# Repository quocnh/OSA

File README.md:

# ESP32_MedicalDevice
IoT devices to collect SPo2 and ECG for cancer treatment.

Downloading Repo from Github
---------------------------------------------------------------------------------------------------------------------------
- 1.) Navigate to "https://github.com/quocnh/OSA_Medical_Devices"
- 2.) Copy HTTPS link
- 3.) Open Git Bash in a local folder
- 4.) enter "git clone <Insert HTTP link here>"
---------------------------------------------------------------------------------------------------------------------------

Installing Firmware to ESP32
---------------------------------------------------------------------------------------------------------------------------
- 1.) Add ESP32 boards to Arduino IDE
	-File -> Preferences 
	-Enter "https://dl.espressif.com/dl/package_esp32_index.json" into "Additional Board Manager URLs" field
	-Tools -> Board -> Boards Manager...
	-Find "esp32" and install version 1.05
- 2.) Add necessary libraries to Arduino IDE
	-Sketch -> Include Library -> Add .ZIP library
	-Select .ZIP from "libraries" folder
	-Repeat for all libraries in the "libraries" folder

   	ArduinoHtppClient (0.5.0)
  	NTPClient(3.2.1)
  	AduinoJson(6.21.4)
  	AutoConnect(1.4.2)
  	PageBuilder(1.5.6)
  	PubSubCleint(2.8)
  	TPBubSupClient(2.9.1)
  	Thingsboard(0.10.2)
  
- 3.) Upload sketch to ESP32
	-Tools -> Board -> ESP32 dev module
	-Tools -> upload speed -> 115200
	-Tools -> Port -> select your COM port
	(https://www.silabs.com/developers/usb-to-uart-bridge-vcp-drivers?tab=downloads) iff missing driver
	-upload (arrow symbol)
	-If connection doesn't work, close sketch, disconnect and reconnect USB, reopen sketch and upload
---------------------------------------------------------------------------------------------------------------------------

Opening Thingsboard Dashboard
---------------------------------------------------------------------------------------------------------------------------
- 1.) Open "http://134.129.97.131:8080/" and sign in
	-login: "tenant@thingsboard.org"
	-password: "tenant"
- 2.) Navigate to ESP32 dashboard
	-Dashboard groups -> ESP32 -> Devkit Test
---------------------------------------------------------------------------------------------------------------------------

WiFi Autoconnect
---------------------------------------------------------------------------------------------------------------------------
- 1.) Power on programmed device and connect to the SpO2ap/ECGap with the default password "12345678"
- 2.) Navigate to "192.168.10.101/_ac" with SpO2ap and "192.168.10.102/_ac" with ECGap on your mobile device's web browser
- 3.) Press settings icon
- 4.) Press menu icon
- 5.) Add wifi network credentials
- 6.) Device will now autoconnect to WiFi
---------------------------------------------------------------------------------------------------------------------------

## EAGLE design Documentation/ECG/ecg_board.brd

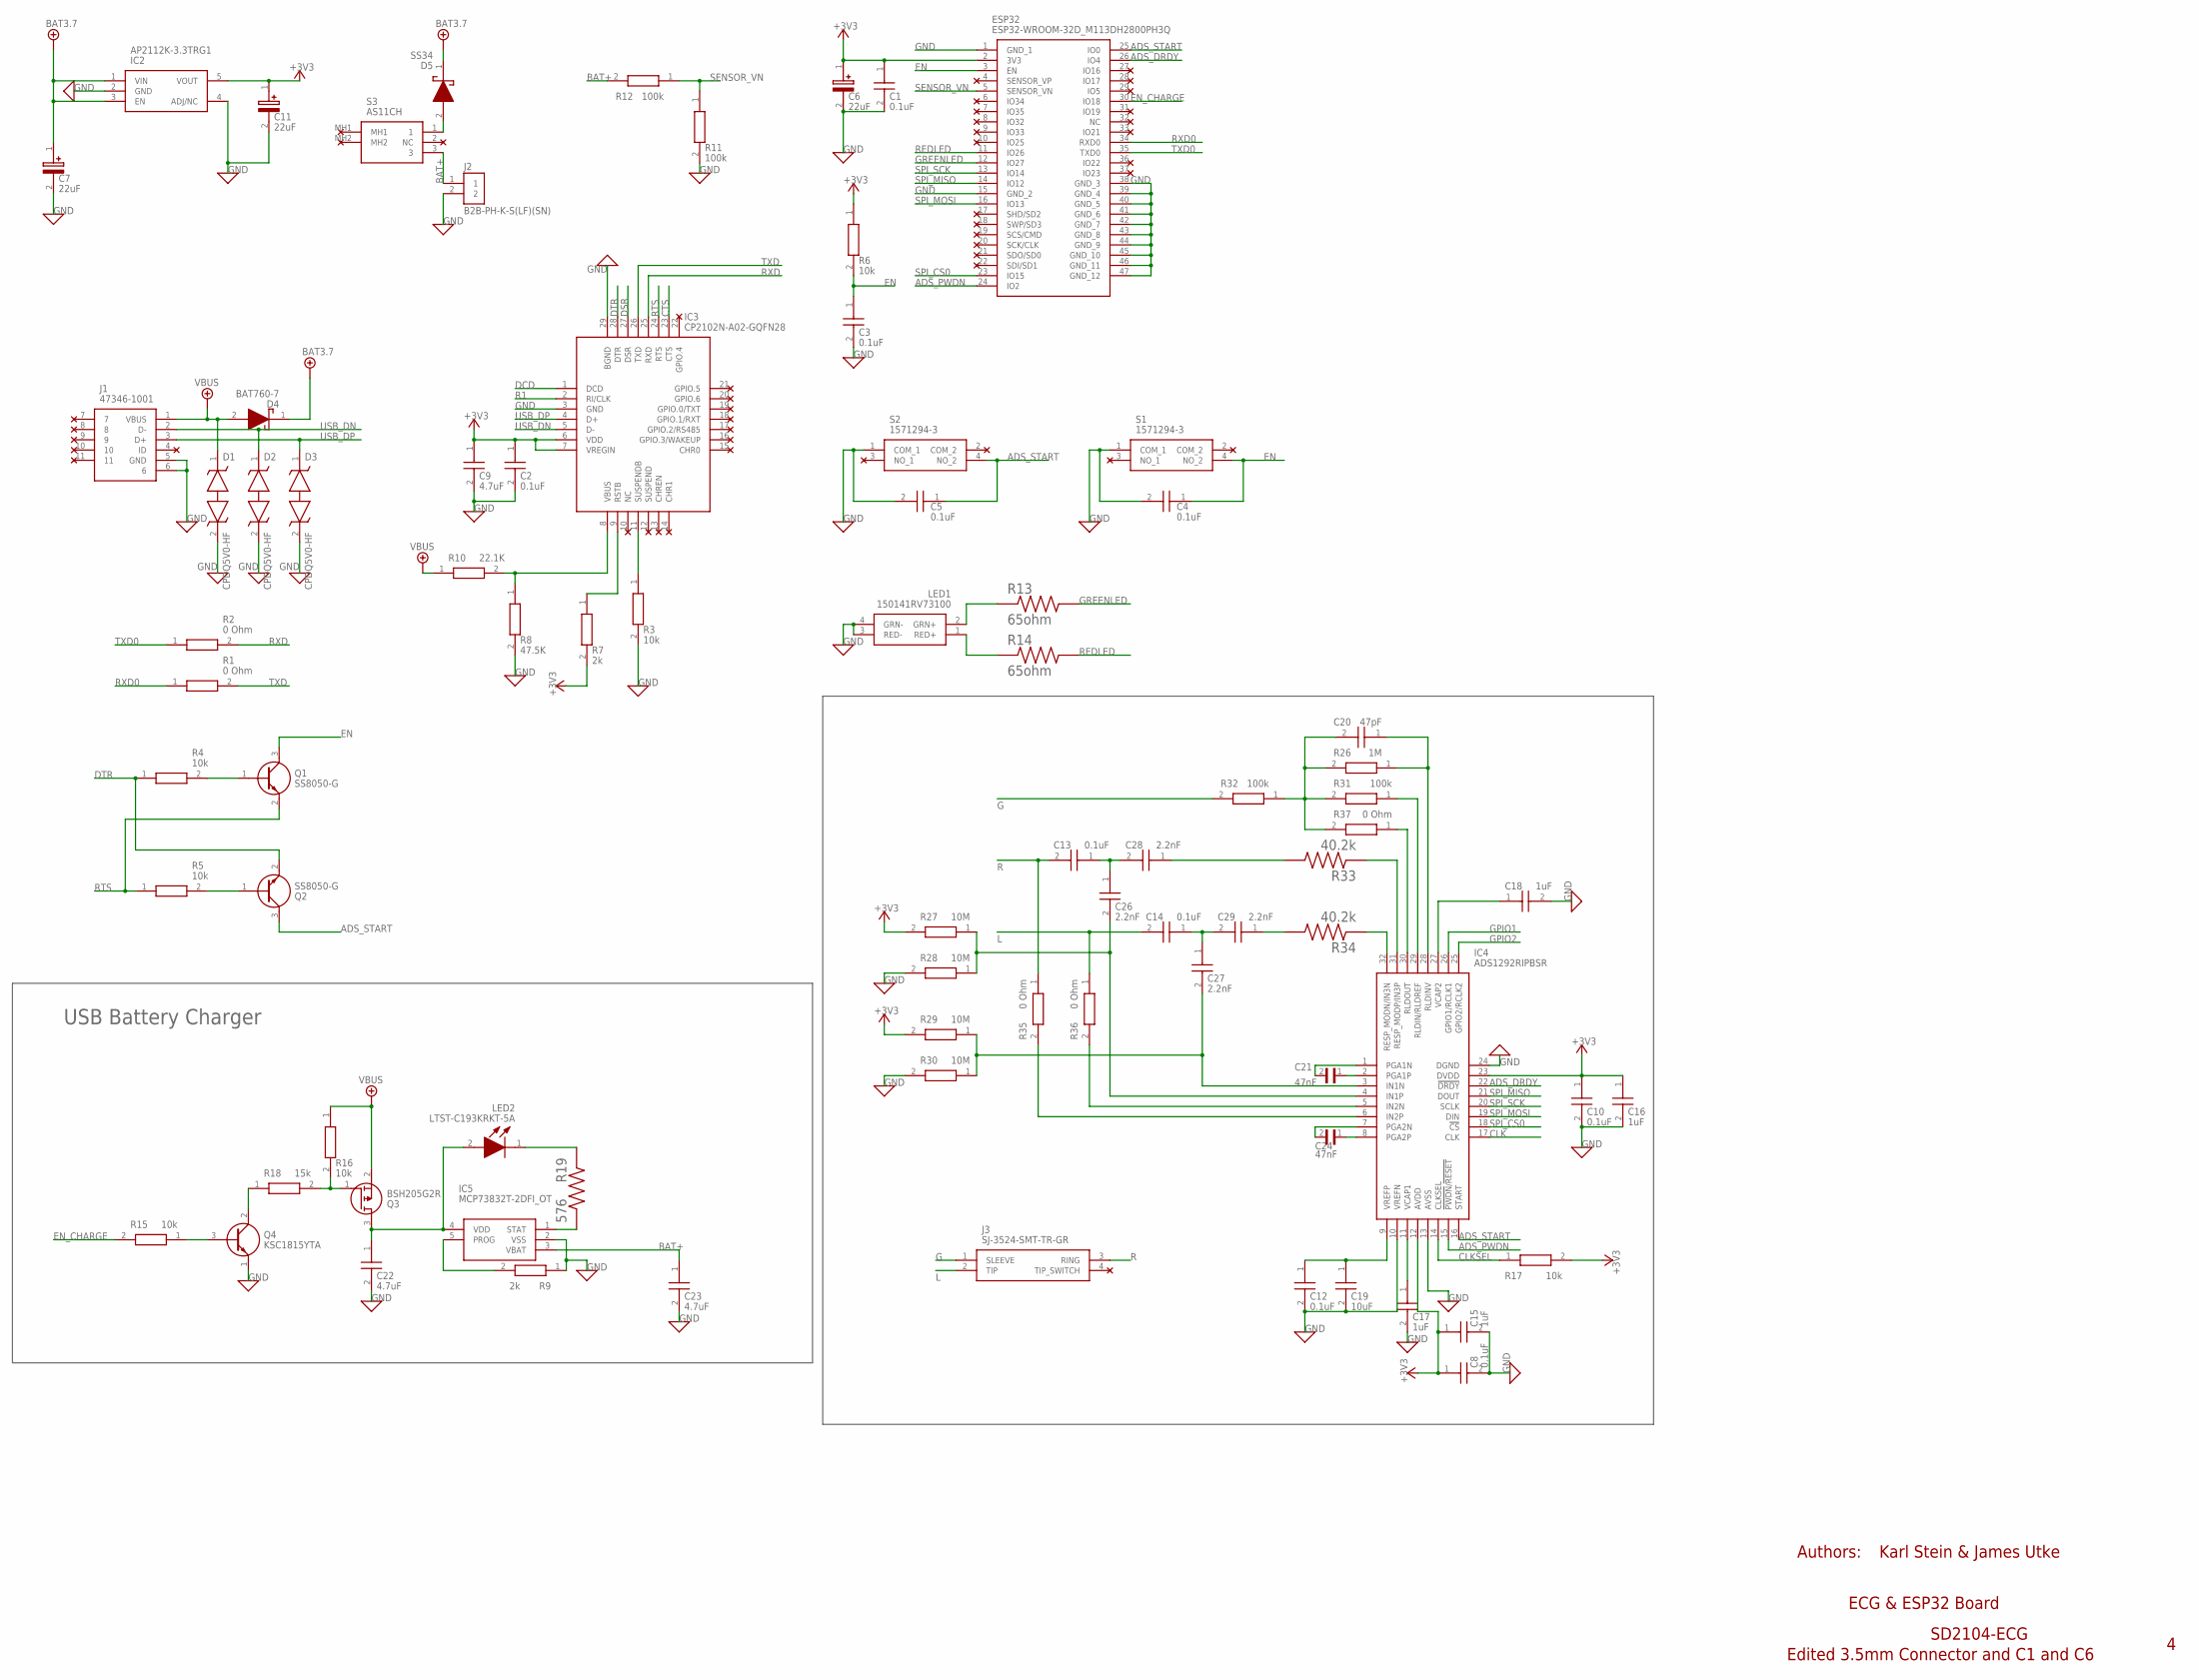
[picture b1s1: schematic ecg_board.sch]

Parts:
C1, C2, C3, C4, C5, C8, C10, C12, C13, C14: 0.1uF; CAPC2012X88N
C6, C7, C11: 22uF; CAPPC1609X90N
C9, C22, C23: 4.7uF; CAPC2114X145N
C15, C16, C17, C18: 1uF; CAPC2012X100N
C19: 10uF; CAPC2012X135N
C20: 47pF; CAPC2012X95N
C21, C24: 47nF; CAPC2012X140N
C26, C27, C28, C29: 2.2nF; CAPC2012X100N
D1, D2, D3: CPDQ5V0-HF; SODFL1006X40N
D4: BAT760-7; SOD2513X120N
D5: SS34; DIOM8059X256N
ESP32: ESP32-WROOM-32D_M113DH2800PH3Q; ESP32WROOM32DM113DH2800PH3Q0
IC2: AP2112K-3.3TRG1; SOT95P282X130-5N
IC3: CP2102N-A02-GQFN28; QFN50P500X500X80-29N
IC4: ADS1292RIPBSR; QFP50P700X700X120-32N
IC5: MCP73832T-2DFI_OT; SOT95P270X145-5N
J1: 47346-1001; 473461001
J2: B2B-PH-K-S(LF)(SN); JST_B2B-PH-K-S(LF)(SN)
J3: SJ-3524-SMT-TR-GR; SJ3524SMTTRGR
LED1: 150141RV73100; SMD3528_1
LED2: LTST-C193KRKT-5A; LEDC1608X45N
Q1, Q2: SS8050-G; SOT95P240X115-3N
Q3: BSH205G2R; SOT95P230X110-3N
Q4: KSC1815YTA; BC33740TA
R1, R2, R35, R36, R37: 0 Ohm; RESC1608X55N
R3, R4, R5, R6, R15, R16, R17: 10k; CAPC1608X55N
R7, R9: 2k; RESC1608X55N
R8: 47.5K; RESC1608X55N
R10: 22.1K; RESC1005X40N
R11, R12, R31, R32: 100k; RESC1608X50N
R13, R14: 65ohm; RESC2012X64N
R18: 15k; RESC2012X60N
R19: 576; RESC2012X50N
R26: 1M; RESC1608X55N
R27, R28, R29, R30: 10M; RESC1608X55N
R33, R34: 40.2k; RESC3216X70N
S1, S2: 1571294-3; 15712943
S3: AS11CH

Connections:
+3V3: C1.1, C2.1, C6.1 (+), C8.1, C9.1, C10.1, C11.1 (+), C15.1, C16.1, ESP32.2 (3V3), IC2.5 (VOUT), IC3.6 (VDD), IC3.7 (VREGIN), IC4.12 (AVDD), IC4.23 (DVDD), R6.1, R7.2, R17.2, R27.2, R29.2
+5V: C7.1 (+), D4.1 (K), D5.1 (K), IC2.1 (VIN), IC2.3 (EN)
+5V/1: D1.1, D4.2 (A), J1.1 (VBUS), Q3.2 (S), R10.1, R16.1
ADS_DRDY: ESP32.26 (IO4), IC4.22 (!DRDY)
ADS_PWDN: ESP32.24 (IO2), IC4.15 (!PWDN!/!RESET)
ADS_START: C5.1, ESP32.25 (IO0), IC4.16 (START), Q2.3 (C), S2.4 (NO_2)
BAT+: C23.1, IC5.3 (VBAT), J2.1, R12.2, S3.3
CLK: IC4.17 (CLK)
CLKSEL: IC4.14 (CLKSEL), R17.1
CTS: IC3.23 (CTS)
DCD: IC3.1 (DCD)
DSR: IC3.27 (DSR)
DTR: IC3.28 (DTR), Q2.2 (E), R4.1
EN: C3.1, C4.1, ESP32.3 (EN), Q1.3 (C), R6.2, S1.4 (NO_2)
EN_CHARGE: ESP32.30 (IO18), R15.2
G: J3.1 (SLEEVE), R32.2
GND: C1.2, C2.2, C3.2, C4.2, C5.2, C6.2 (-), C7.2 (-), C8.2, C9.2, C10.2, C11.2 (-), C12.2, C15.2, C16.2, C17.2, C18.2, C19.2, C22.2, C23.2, D1.2, D2.2, D3.2, ESP32.1 (GND_1), ESP32.15 (GND_2), ESP32.38 (GND_3), ESP32.39 (GND_4), ESP32.40 (GND_5), ESP32.41 (GND_6), ESP32.42 (GND_7), ESP32.43 (GND_8), ESP32.44 (GND_9), ESP32.45 (GND_10), ESP32.46 (GND_11), ESP32.47 (GND_12), IC2.2 (GND), IC2.4 (ADJ/NC), IC3.3 (GND), IC3.29 (BGND), IC4.10 (VREFN), IC4.13 (AVSS), IC4.24 (DGND), IC5.2 (VSS), J1.5 (GND), J1.6, J2.2, LED1.3 (RED-), LED1.4 (GRN-), Q4.1 (E), R3.2, R8.2, R9.1, R11.2, R28.2, R30.2, S1.1 (COM_1), S2.1 (COM_1)
GPIO1: IC4.26 (GPIO1/RCLK1)
GPIO2: IC4.25 (GPIO2/RCLK2)
GREENLED: ESP32.12 (IO27), R13.2
L: C14.2, J3.2 (TIP), R36.1
unnamed: LED1.2 (GRN+), R13.1
unnamed: LED1.1 (RED+), R14.1
unnamed: C12.1, C19.1, IC4.9 (VREFP)
unnamed: Q1.1 (B), R4.2
unnamed: Q2.1 (B), R5.2
unnamed: C17.1, IC4.11 (VCAP1)
unnamed: C18.1, IC4.27 (VCAP2)
unnamed: LED2.1 (K), R19.1
unnamed: IC4.32 (RESP_MODN/IN3N), R34.1
unnamed: D5.2 (A), S3.1
unnamed: IC5.5 (PROG), R9.2
unnamed: Q4.3 (B), R15.1
unnamed: IC4.31 (RESP_MODP/IN3P), R33.1
unnamed: Q4.2 (C), R18.1
unnamed: C29.1, R34.2
unnamed: IC3.11 (SUSPENDB), R3.1
unnamed: IC3.9 (RSTB), R7.1
unnamed: IC3.8 (VBUS), R8.1, R10.2
unnamed: C14.1, C27.1, C29.2
unnamed: C13.1, C26.1, C28.2
unnamed: C28.1, R33.2
unnamed: IC4.5 (IN2N), R36.2
unnamed: IC4.6 (IN2P), R35.2
unnamed: Q3.1 (G), R16.2, R18.2
unnamed: IC5.1 (STAT), R19.2
unnamed: C20.2, R26.2, R31.2, R32.1, R37.2
unnamed: C22.1, IC5.4 (VDD), LED2.2 (A), Q3.3 (D)
unnamed: C21.1, IC4.2 (PGA1P)
unnamed: C21.2, IC4.1 (PGA1N)
unnamed: C27.2, IC4.3 (IN1N), R29.1, R30.1
unnamed: C26.2, IC4.4 (IN1P), R27.1, R28.1
unnamed: C24.1, IC4.8 (PGA2P)
unnamed: C24.2, IC4.7 (PGA2N)
unnamed: IC4.29 (RLDIN/RLDREF), R31.1
unnamed: IC4.30 (RLDOUT), R37.1
unnamed: C20.1, IC4.28 (RLDINV), R26.1
R: C13.2, J3.3 (RING), R35.1
R1: IC3.2 (RI/CLK)
REDLED: ESP32.11 (IO26), R14.2
RTS: IC3.24 (RTS), Q1.2 (E), R5.1
RXD: IC3.25 (RXD), R2.2
RXD0: ESP32.34 (RXD0), R1.1
SENSOR_VN: ESP32.5 (SENSOR_VN), R11.1, R12.1
SPI_CS0: ESP32.23 (IO15), IC4.18 (!CS)
SPI_MISO: ESP32.14 (IO12), IC4.21 (DOUT)
SPI_MOSI: ESP32.16 (IO13), IC4.19 (DIN)
SPI_SCK: ESP32.13 (IO14), IC4.20 (SCLK)
TXD: IC3.26 (TXD), R1.2
TXD0: ESP32.35 (TXD0), R2.1
USB_DN: D2.1, IC3.5 (D-), J1.2 (D-)
USB_DP: D3.1, IC3.4 (D+), J1.3 (D+)

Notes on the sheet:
ECG & ESP32 Board
Authors:
Karl Stein & James Utke
SD2104-ECG
USB Battery Charger
Edited 3.5mm Connector and C1 and C6

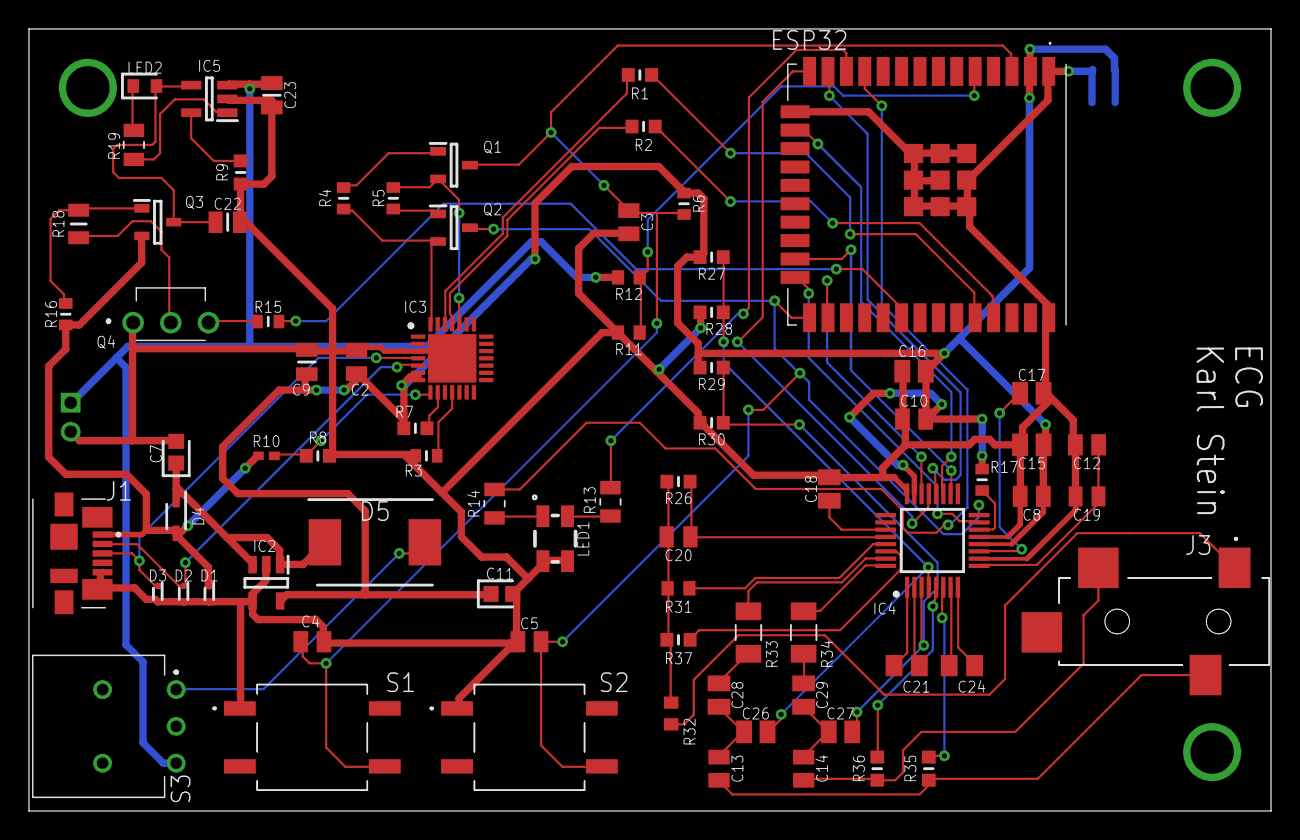
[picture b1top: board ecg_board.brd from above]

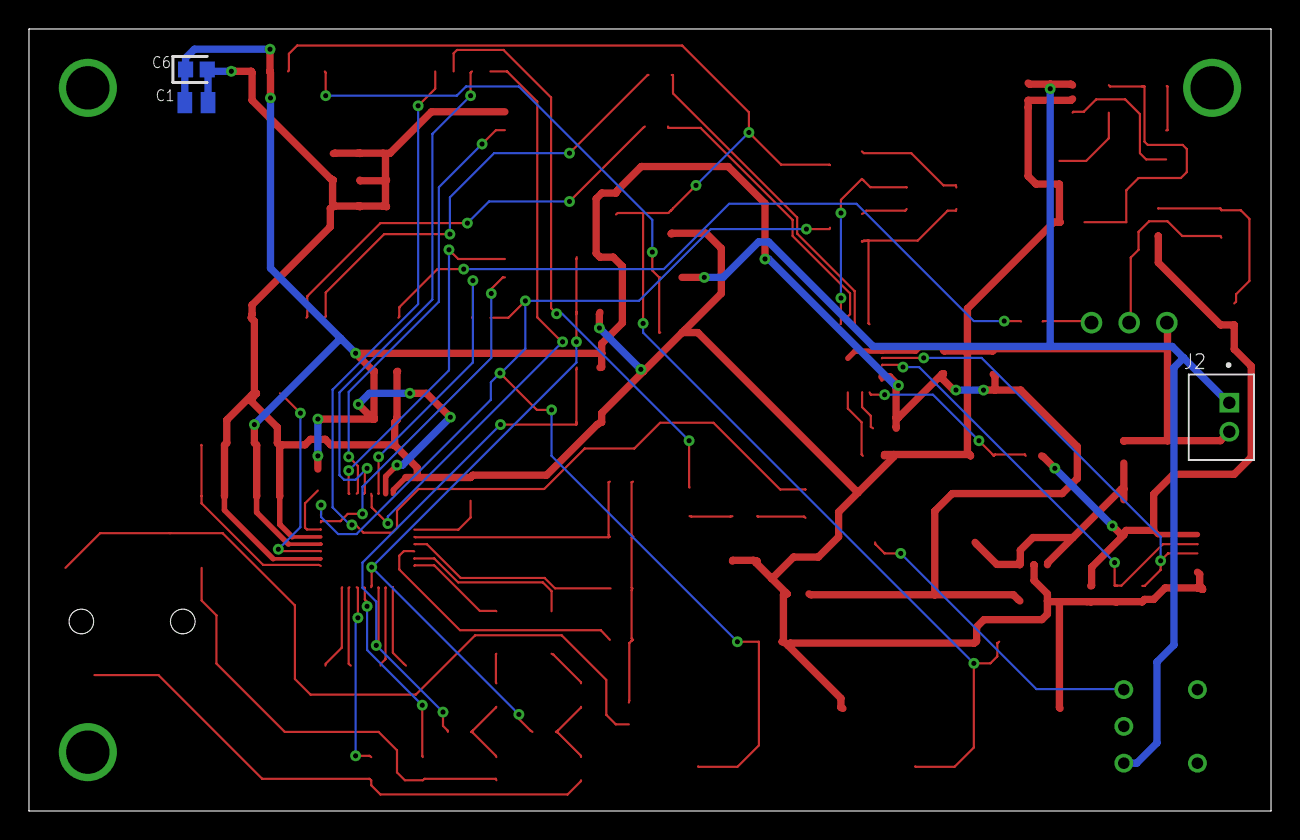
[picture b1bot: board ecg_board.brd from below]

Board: 2 copper layers, 85.7 x 54.0 mm, 81 parts (3 on the bottom side), 65 nets.

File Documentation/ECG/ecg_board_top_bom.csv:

Comment,Designator,Footprint,LCSC Part #
0 Ohm,R1 R2 R35 R36 R37,RESC1608X55N,
0.1uF,C2 C3 C4 C5 C8 C10 C12 C13 C14,CAPC2012X88N,
1M,R26,RESC1608X55N,
1uF,C15 C16 C17 C18,CAPC2012X100N,
2.2nF,C26 C27 C28 C29,CAPC2012X100N,
2k,R7 R9,RESC1608X55N,
4.7uF,C9 C22 C23,CAPC2114X145N,
10M,R27 R28 R29 R30,RESC1608X55N,
10k,R3 R4 R5 R6 R15 R16 R17,CAPC1608X55N,
10uF,C19,CAPC2012X135N,
15k,R18,RESC2012X60N,
22.1K,R10,RESC1005X40N,
22uF,C7 C11,CAPPC1609X90N,
40.2k,R33 R34,RESC3216X70N,
47.5K,R8,RESC1608X55N,
47nF,C21 C24,CAPC2012X140N,
47pF,C20,CAPC2012X95N,
65ohm,R13 R14,RESC2012X64N,
100k,R11 R12 R31 R32,RESC1608X50N,
576,R19,RESC2012X50N,
47346-1001,J1,473461001,
150141RV73100,LED1,SMD3528_1,
1571294-3,S1 S2,15712943,
ADS1292RIPBSR,IC4,QFP50P700X700X120-32N,
AP2112K-3.3TRG1,IC2,SOT95P282X130-5N,
BAT760-7,D4,SOD2513X120N,
BSH205G2R,Q3,SOT95P230X110-3N,
CP2102N-A02-GQFN28,IC3,QFN50P500X500X80-29N,
CPDQ5V0-HF,D1 D2 D3,SODFL1006X40N,
ESP32-WROOM-32D_M113DH2800PH3Q,ESP32,ESP32WROOM32DM113DH2800PH3Q0,
LTST-C193KRKT-5A,LED2,LEDC1608X45N,
MCP73832T-2DFI_OT,IC5,SOT95P270X145-5N,
SJ-3524-SMT-TR-GR,J3,SJ3524SMTTRGR,
SS34,D5,DIOM8059X256N,
SS8050-G,Q1 Q2,SOT95P240X115-3N,

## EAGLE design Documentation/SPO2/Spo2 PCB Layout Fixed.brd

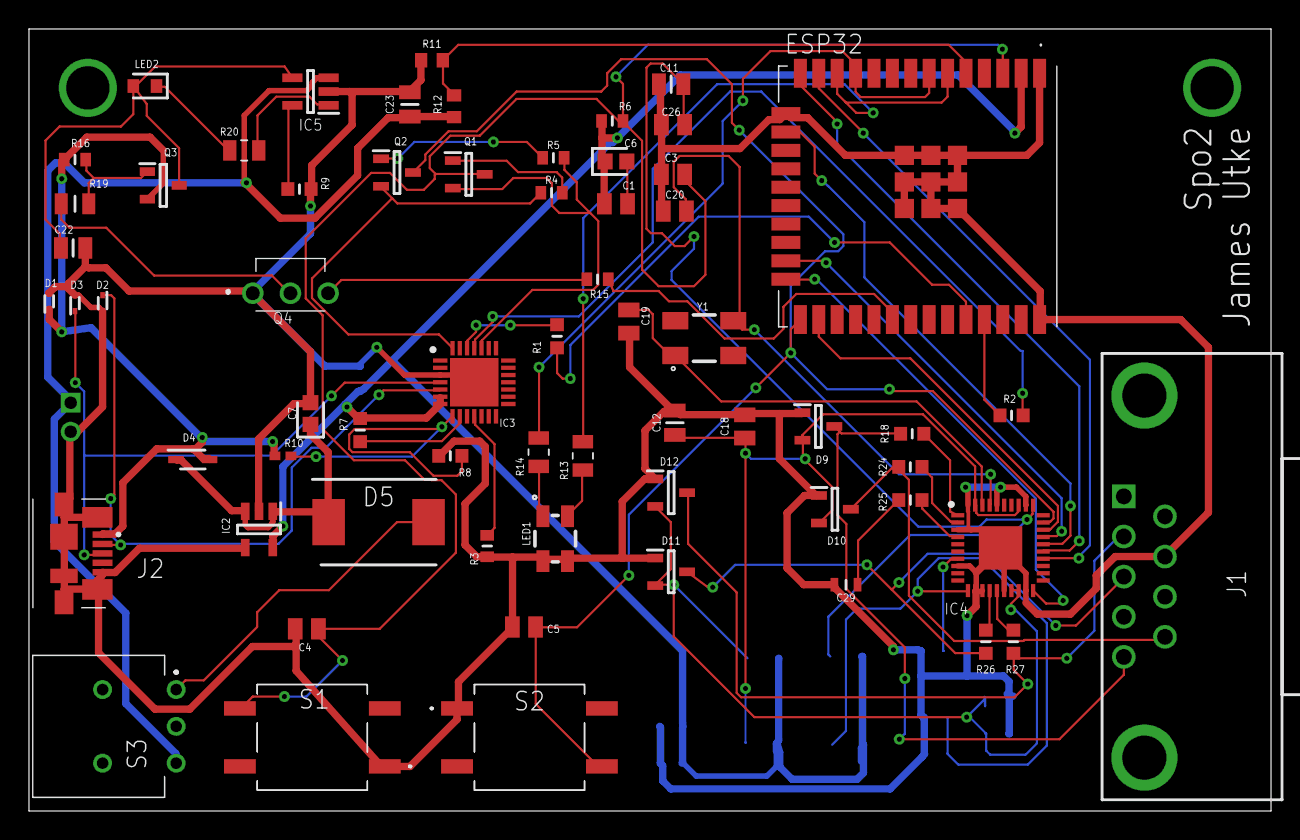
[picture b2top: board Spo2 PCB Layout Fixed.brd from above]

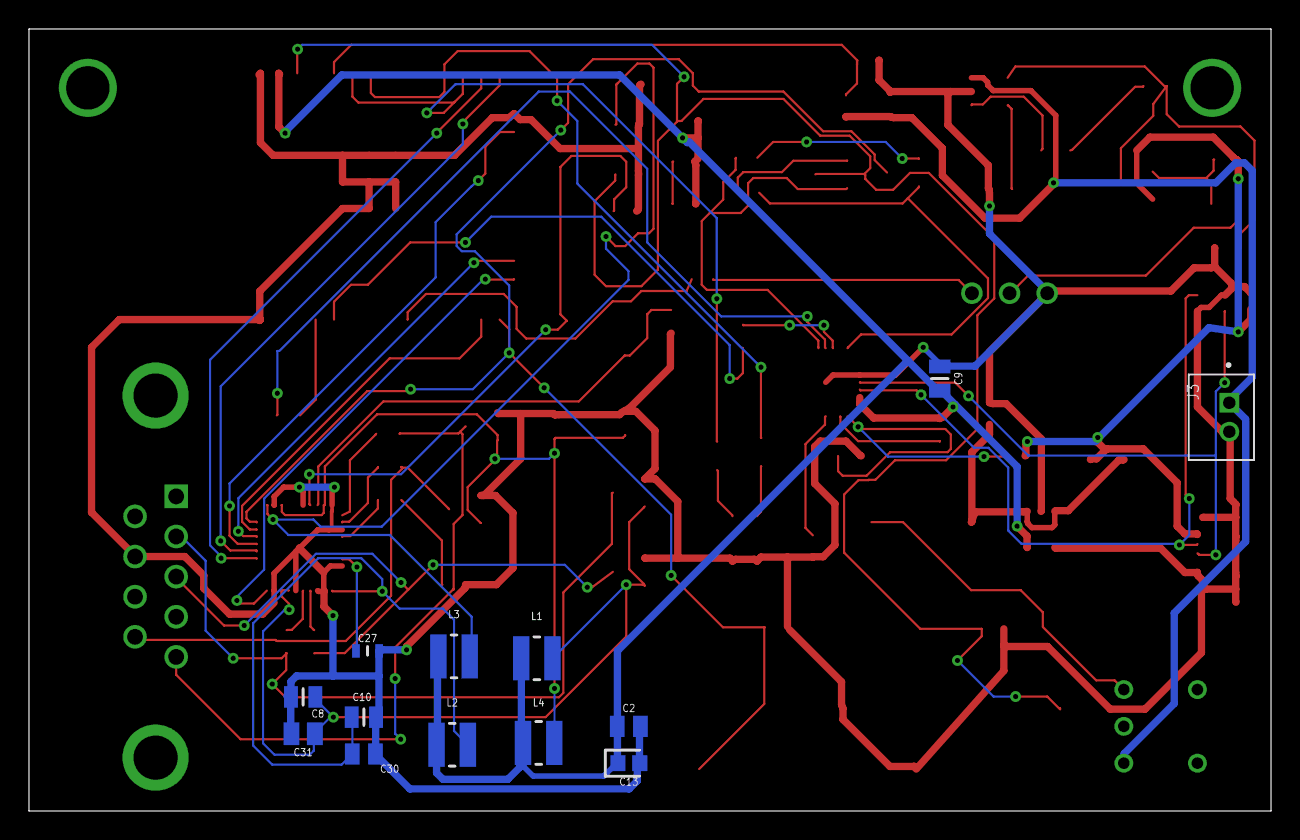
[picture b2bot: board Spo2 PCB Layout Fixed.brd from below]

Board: 2 copper layers, 85.7 x 54.0 mm, 77 parts (13 on the bottom side), 58 nets.

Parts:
C1, C2, C3, C4, C5, C18, C26, C30: 0.1uF; CAPC2012X88N
C6, C7, C13: 22uF; CAPPC1609X90N
C8, C10, C11, C12: 10uF; CAPC2114X145N@1
C9, C22, C23: 4.7uF; CAPC2114X145N
C19, C20: 22pF; CAPC2012X88N@1
C27, C29: 2.2uF; CAPC1608X80N
C31: 1uF; CAPC2012X100N
D1, D2, D3: CPDQ5V0-HF; SODFL1006X40N
D4: BAT760-7; SOD2513X120N
D5: SS34; DIOM8059X256N
D9, D10, D11, D12: BAT54S; SOT95P240X110-3N
ESP32: ESP32-WROOM-32D_M113DH2800PH3Q; ESP32WROOM32DM113DH2800PH3Q0
IC2: AP2112K-3.3TRG1; SOT95P282X130-5N
IC3: CP2102N-A02-GQFN28; QFN50P500X500X80-29N
IC4: AFE4400RHAR; QFN50P600X600X100-41N
IC5: MCP73832T-2DFI_OT; SOT95P270X145-5N
J1: 182-009-213R161; 182009213R161
J2: 47346-1001; 473461001
J3: B2B-PH-K-S(LF)(SN); JST_B2B-PH-K-S(LF)(SN)
L1, L2, L3, L4: 470nH; LPS3010471MRC
LED1: 150141RV73100; SMD3528_1
LED2: LTST-C193KRKT-5A; LEDC1608X45N
Q1, Q2: SS8050-G; SOT95P240X115-3N
Q3: BSH205G2R; SOT95P230X110-3N
Q4: KSC1815YTA; BC33740TA
R1, R2, R18, R24, R25, R26, R27: 0 Ohm; RESC1608X55N
R3, R4, R5, R6, R15, R16: 10k; CAPC1608X55N
R7, R9: 2k; RESC1608X55N
R8: 47.5K; RESC1608X55N
R10: 22.1K; RESC1005X40N
R11, R12: 100k; RESC1608X50N
R13, R14: 65ohm; RESC2012X64N
R19: 15k; RESC2012X60N
R20: 576; RESC2012X50N
S1, S2: 1571294-3; 15712943
S3: AS11CH
Y1: ABM3B-8.000MHZ-10-1-U-T; ABM3B

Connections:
0: C1.2, C6.2
!ADC_RESET: C5.1, ESP32.25, IC4.29, Q2.3, S2.4
!AFE_PDN: ESP32.24, IC4.20
+3V3: C1.1, C2.1, C6.1, C9.1, C13.1, ESP32.2, IC2.5, IC3.6, IC3.7, L1.1, L2.1, L3.1, L4.1, R6.1, R7.2
+5V: C7.1, D4.1, D5.1, IC2.1, IC2.3
+5V/1: D1.1, D4.2, J2.1, Q3.2, R10.1, R16.1
ADC_RDY: ESP32.26, IC4.28
BAT+: C23.1, IC5.3, J3.1, R12.2, S3.3
DTR: IC3.28, Q2.2, R4.1
EN: C3.1, C4.1, ESP32.3, Q1.3, R6.2, S1.4
EN_CHARGE: ESP32.30, R15.2
GND: C2.2, C3.2, C4.2, C5.2, C7.2, C8.2, C9.2, C10.2, C11.2, C12.2, C13.2, C18.2, C19.2, C20.2, C22.2, C23.2, C26.2, C27.2, C29.2, C30.2, C31.2, D1.2, D2.2, D3.2, D9.1, D10.1, D11.1, D12.1, ESP32.1, ESP32.15, ESP32.38, ESP32.39, ESP32.40, ESP32.41, ESP32.42, ESP32.43, ESP32.44, ESP32.45, ESP32.46, ESP32.47, IC2.2, IC2.4, IC3.3, IC3.29, IC4.3, IC4.8, IC4.12, IC4.13, IC4.16, IC4.19, IC4.32, IC4.36, IC4.40, IC4.41, IC5.2, J1.7, J2.5, J2.6, J2.7, J2.8, J2.9, J2.10, J2.11, J3.2, LED1.3, LED1.4, Q4.1, R3.2, R8.2, R9.1, R11.2, S1.1, S2.1
GREENLED: ESP32.6, ESP32.12, R13.2
INN: D9.3, J1.5, R18.2
INP: D10.3, J1.9, R24.2
LED_DRV_SUP: C8.1, C31.1, D11.2, D12.2, IC4.17, IC4.18, L1.2
unnamed: LED1.2, R13.1
unnamed: LED1.1, R14.1
unnamed: C19.1, IC4.38, Y1.1
unnamed: Q1.1, R4.2
unnamed: Q2.1, R5.2
unnamed: IC5.5, R9.2
unnamed: C20.1, IC4.37, Y1.3
unnamed: C27.1, IC4.7
unnamed: IC4.1, R18.1
unnamed: IC4.2, R24.1
unnamed: IC4.14, R26.1
unnamed: C29.1, R25.2
unnamed: IC4.15, R27.1
unnamed: Q4.3, R15.1
unnamed: Q4.2, R19.1
unnamed: IC3.11, R3.1
unnamed: IC3.9, R7.1
unnamed: IC3.8, R8.1, R10.2
unnamed: LED2.1, R20.1
unnamed: D5.2, S3.1
unnamed: Q3.1, R16.2, R19.2
unnamed: IC5.1, R20.2
unnamed: C22.1, IC5.4, LED2.2, Q3.3
REDLED: ESP32.7, ESP32.11, R14.2
RTS: IC3.24, Q1.2, R5.1
RXD: IC3.25, R2.2
RXD0: ESP32.34, R1.1
RX_ANA_SUP: C12.1, C18.1, D9.2, D10.2, IC4.33, IC4.39, L4.2
RX_DIG_SUP: C11.1, C26.1, IC4.31, L3.2
SENSOR_VN: ESP32.5, R11.1, R12.1
SPI_CS0: ESP32.23, IC4.27
SPI_MISO: ESP32.14, IC4.25
SPI_MOSI: ESP32.16, IC4.26
SPI_SCK: ESP32.13, IC4.24
TXD: IC3.26, R1.2
TXD0: ESP32.35, R2.1
TXN: D11.3, J1.3, R26.2
TXP: D12.3, J1.2, R27.2
TX_CTRL_SUP: C10.1, C30.1, IC4.11, L2.2
USB_DN: D2.1, IC3.5, J2.2
USB_DP: D3.1, IC3.4, J2.3
VCM: IC4.4, R25.1

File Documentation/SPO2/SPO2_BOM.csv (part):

"Part";"Value";"Device";"Package";"Description";"ARROW_PART_NUMBER";"ARROW_PRICE-STOCK";"DESCRIPTION";"DIGI-KEY_PART_NUMBER";"HEIGHT";"MANUFACTURER_NAME";"MANUFACTURER_PART_NUMBER";"MF";"MOUSER_PART_NUMBER";"MOUSER_PRICE-STOCK";"MP";"PACKAGE";"PURCHASE-URL";"VALUE";
"C1";"0.1uF";"C0805C104K5RAC7411";"CAPC2012X88N";"Cap Ceramic 0.1uF 50V X7R 10% Pad SMD 0805 125C T/R";"";"";"Cap Ceramic 0.1uF 50V X7R 10% Pad SMD 0805 125C T/R";"";"0.88mm";"Kemet";"C0805C104K5RAC7411";"";"80-C0805C104K5RACLR";"https://www.mouser.co.uk/ProductDetail/KEMET/C0805C104K5RAC7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";"";"";"";"0.1uF";
"C2";"0.1uF";"C0805C104K5RAC7411";"CAPC2012X88N";"Cap Ceramic 0.1uF 50V X7R 10% Pad SMD 0805 125C T/R";"";"";"Cap Ceramic 0.1uF 50V X7R 10% Pad SMD 0805 125C T/R";"";"0.88mm";"Kemet";"C0805C104K5RAC7411";"";"80-C0805C104K5RACLR";"https://www.mouser.co.uk/ProductDetail/KEMET/C0805C104K5RAC7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";"";"";"";"0.1uF";
"C3";"0.1uF";"C0805C104K5RAC7411";"CAPC2012X88N";"Cap Ceramic 0.1uF 50V X7R 10% Pad SMD 0805 125C T/R";"";"";"Cap Ceramic 0.1uF 50V X7R 10% Pad SMD 0805 125C T/R";"";"0.88mm";"Kemet";"C0805C104K5RAC7411";"";"80-C0805C104K5RACLR";"https://www.mouser.co.uk/ProductDetail/KEMET/C0805C104K5RAC7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";"";"";"";"0.1uF";
"C4";"0.1uF";"C0805C104K5RAC7411";"CAPC2012X88N";"Cap Ceramic 0.1uF 50V X7R 10% Pad SMD 0805 125C T/R";"";"";"Cap Ceramic 0.1uF 50V X7R 10% Pad SMD 0805 125C T/R";"";"0.88mm";"Kemet";"C0805C104K5RAC7411";"";"80-C0805C104K5RACLR";"https://www.mouser.co.uk/ProductDetail/KEMET/C0805C104K5RAC7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";"";"";"";"0.1uF";
"C5";"0.1uF";"C0805C104K5RAC7411";"CAPC2012X88N";"Cap Ceramic 0.1uF 50V X7R 10% Pad SMD 0805 125C T/R";"";"";"Cap Ceramic 0.1uF 50V X7R 10% Pad SMD 0805 125C T/R";"";"0.88mm";"Kemet";"C0805C104K5RAC7411";"";"80-C0805C104K5RACLR";"https://www.mouser.co.uk/ProductDetail/KEMET/C0805C104K5RAC7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";"";"";"";"0.1uF";
"C6";"22uF";"F381A226MMAAXE";"CAPPC1609X90N";"22uF F38 Series Conductive Polymer, Miniature, Undertab Solid Electrolytic Chip Capacitors";"";"";"22uF F38 Series Conductive Polymer, Miniature, Undertab Solid Electrolytic Chip Capacitors";"";"0.9mm";"AVX";"F381A226MMAAXE";"";"581-F381A226MMAAXE";"https://www.mouser.co.uk/ProductDetail/AVX/F381A226MMAAXE?qs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";"";"";"";"22uF";
"C7";"22uF";"F381A226MMAAXE";"CAPPC1609X90N";"22uF F38 Series Conductive Polymer, Miniature, Undertab Solid Electrolytic Chip Capacitors";"";"";"22uF F38 Series Conductive Polymer, Miniature, Undertab Solid Electrolytic Chip Capacitors";"";"0.9mm";"AVX";"F381A226MMAAXE";"";"581-F381A226MMAAXE";"https://www.mouser.co.uk/ProductDetail/AVX/F381A226MMAAXE?qs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";"";"";"";"22uF";
"C8";"10uF";"TMK212BC6106KG-T";"CAPC2114X145N@1";"Status\tMass Production (Preferred) Capacitance\t10 uF +/- 10 % Case Size (EIA/JIS)\t0805/2012 Rated Voltage\t25 V tan (max)\t10 % Temperature Characteristic (EIA)\tX6S Operating Temp. Range (EIA)\t-55 to +105  High Temperature Loading (% Rated Voltage)\t150 % Insulation Resistance (min)\t100 MuF Dimension L\t2.0 +0.20/-0.00 mm Dimension W\t1.25 +0.20/-0.00 mm Dimension T\t1.25 +0.20/-0.00 mm Dimension e\t0.50 +/-0.25 mm RoHS Compliance (10 subst.)\tYes REACH Compliance (205 subst.)\tYes IEC62474 (Ver. D19";"";"";"Status Mass Production (Preferred) Capacitance 10 uF +/- 10 % Case Size (EIA/JIS) 0805/2012 Rated Voltage 25 V tan (max) 10 % Temperature Characteristic (EIA) X6S Operating Temp. Range (EIA) -55 to +105  High Temperature Loading (% Rated Voltage) 150 % Insulation Resistance (min) 100 MuF Dimension L 2.0 +0.20/-0.00 mm Dimension W 1.25 +0.20/-0.00 mm Dimension T 1.25 +0.20/-0.00 mm Dimension e 0.50 +/-0.25 mm RoHS Compliance (10 subst.) Yes REACH Compliance (205 subst.) Yes IEC62474 (Ver. D19";"";"1.45mm";"TAIYO YUDEN";"TMK212BC6106KG-T";"";"963-TMK212BC6106KG-T";"https://www.mouser.co.uk/ProductDetail/Taiyo-Yuden/TMK212BC6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";"";"";"";"";
"C9";"4.7uF";"JMK212B7475KGHT";"CAPC2114X145N";"Taiyo Yuden JMK212B7475KGHT 4.7F MLCC 6.3V dc +/-10% Tolerance SMD";"";"";"Taiyo Yuden JMK212B7475KGHT 4.7F MLCC 6.3V dc +/-10% Tolerance SMD";"";"1.45mm";"TAIYO YUDEN";"JMK212B7475KGHT";"";"963-JMK212B7475KGHT";"https://www.mouser.co.uk/ProductDetail/Taiyo-Yuden/JMK212B74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";"";"";"";"4.7uF";
"C10";"10uF";"TMK212BC6106KG-T";"CAPC2114X145N@1";"Status\tMass Production (Preferred) Capacitance\t10 uF +/- 10 % Case Size (EIA/JIS)\t0805/2012 Rated Voltage\t25 V tan (max)\t10 % Temperature Characteristic (EIA)\tX6S Operating Temp. Range (EIA)\t-55 to +105  High Temperature Loading (% Rated Voltage)\t150 % Insulation Resistance (min)\t100 MuF Dimension L\t2.0 +0.20/-0.00 mm Dimension W\t1.25 +0.20/-0.00 mm Dimension T\t1.25 +0.20/-0.00 mm Dimension e\t0.50 +/-0.25 mm RoHS Compliance (10 subst.)\tYes REACH Compliance (205 subst.)\tYes IEC62474 (Ver. D19";"";"";"Status Mass Production (Preferred) Capacitance 10 uF +/- 10 % Case Size (EIA/JIS) 0805/2012 Rated Voltage 25 V tan (max) 10 % Temperature Characteristic (EIA) X6S Operating Temp. Range (EIA) -55 to +105  High Temperature Loading (% Rated Voltage) 150 % Insulation Resistance (min) 100 MuF Dimension L 2.0 +0.20/-0.00 mm Dimension W 1.25 +0.20/-0.00 mm Dimension T 1.25 +0.20/-0.00 mm Dimension e 0.50 +/-0.25 mm RoHS Compliance (10 subst.) Yes REACH Compliance (205 subst.) Yes IEC62474 (Ver. D19";"";"1.45mm";"TAIYO YUDEN";"TMK212BC6106KG-T";"";"963-TMK212BC6106KG-T";"https://www.mouser.co.uk/ProductDetail/Taiyo-Yuden/TMK212BC6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";"";"";"";"";
"C11";"10uF";"TMK212BC6106KG-T";"CAPC2114X145N@1";"Status\tMass Production (Preferred) Capacitance\t10 uF +/- 10 % Case Size (EIA/JIS)\t0805/2012 Rated Voltage\t25 V tan (max)\t10 % Temperature Characteristic (EIA)\tX6S Operating Temp. Range (EIA)\t-55 to +105  High Temperature Loading (% Rated Voltage)\t150 % Insulation Resistance (min)\t100 MuF Dimension L\t2.0 +0.20/-0.00 mm Dimension W\t1.25 +0.20/-0.00 mm Dimension T\t1.25 +0.20/-0.00 mm Dimension e\t0.50 +/-0.25 mm RoHS Compliance (10 subst.)\tYes REACH Compliance (205 subst.)\tYes IEC62474 (Ver. D19";"";"";"Status Mass Production (Preferred) Capacitance 10 uF +/- 10 % Case Size (EIA/JIS) 0805/2012 Rated Voltage 25 V tan (max) 10 % Temperature Characteristic (EIA) X6S Operating Temp. Range (EIA) -55 to +105  High Temperature Loading (% Rated Voltage) 150 % Insulation Resistance (min) 100 MuF Dimension L 2.0 +0.20/-0.00 mm Dimension W 1.25 +0.20/-0.00 mm Dimension T 1.25 +0.20/-0.00 mm Dimension e 0.50 +/-0.25 mm RoHS Compliance (10 subst.) Yes REACH Compliance (205 subst.) Yes IEC62474 (Ver. D19";"";"1.45mm";"TAIYO YUDEN";"TMK212BC6106KG-T";"";"963-TMK212BC6106KG-T";"https://www.mouser.co.uk/ProductDetail/Taiyo-Yuden/TMK212BC6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";"";"";"";"";
"C12";"10uF";"TMK212BC6106KG-T";"CAPC2114X145N@1";"Status\tMass Production (Preferred) Capacitance\t10 uF +/- 10 % Case Size (EIA/JIS)\t0805/2012 Rated Voltage\t25 V tan (max)\t10 % Temperature Characteristic (EIA)\tX6S Operating Temp. Range (EIA)\t-55 to +105  High Temperature Loading (% Rated Voltage)\t150 % Insulation Resistance (min)\t100 MuF Dimension L\t2.0 +0.20/-0.00 mm Dimension W\t1.25 +0.20/-0.00 mm Dimension T\t1.25 +0.20/-0.00 mm Dimension e\t0.50 +/-0.25 mm RoHS Compliance (10 subst.)\tYes REACH Compliance (205 subst.)\tYes IEC62474 (Ver. D19";"";"";"Status Mass Production (Preferred) Capacitance 10 uF +/- 10 % Case Size (EIA/JIS) 0805/2012 Rated Voltage 25 V tan (max) 10 % Temperature Characteristic (EIA) X6S Operating Temp. Range (EIA) -55 to +105  High Temperature Loading (% Rated Voltage) 150 % Insulation Resistance (min) 100 MuF Dimension L 2.0 +0.20/-0.00 mm Dimension W 1.25 +0.20/-0.00 mm Dimension T 1.25 +0.20/-0.00 mm Dimension e 0.50 +/-0.25 mm RoHS Compliance (10 subst.) Yes REACH Compliance (205 subst.) Yes IEC62474 (Ver. D19";"";"1.45mm";"TAIYO YUDEN";"TMK212BC6106KG-T";"";"963-TMK212BC6106KG-T";"https://www.mouser.co.uk/ProductDetail/Taiyo-Yuden/TMK212BC6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";"";"";"";"";
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
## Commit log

2023-03-28 Create Install_ThingsboardPE_AWS
2023-03-30 Create WIKI
2023-04-03 Update Install_ThingsboardPE_AWS
2023-12-15 Rename osa_gerber_kicad.zip to gerber_osa_gerber_kicad.zip
2023-12-21 work well, dec 21, 2023
